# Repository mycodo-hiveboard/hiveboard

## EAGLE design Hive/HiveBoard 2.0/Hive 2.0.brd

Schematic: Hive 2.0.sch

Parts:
C1, C5: 470uF; PANASONIC_C
C1A1, C1A2, C1B1, C1B2: 1uf 50v; UD-4X5,8_NICHICON
C2, C3, C6, C9: 100uF; PANASONIC_C
C4, C18: 470pF; 0805
C7: 10uF; 0402
C8, C10, C11, C12, C13, C14, C15, C16, C17: 0.1uF; 0805
D1, D2: 1N5819-B; DO41-7.6
D4, D6, D8, D10, D12, D14, D16, D18, D20, D22, D24, D26: 1N4148; SOD-323
D5, D7, D9, D11, D13, D15, D17, D19, D21, D23, D25, D27: RED; CHIPLED_0805_NOOUTLINE
H1, H2, H3, H4: STAND-OFF
IC2: LTC4311_SC70; SC70-6L
J1, J3: C2886705; 1X04
J6, J7: Vertical Qwiic Connector; JST04_1MM_VERT
J8: POWER_JACK; POWER_JACK_PTH
JP1, JP2, JP3: HEADER-1X3ROUND; 1X03_ROUND
JP4, JP32, JP33: HEADER-1X12MM; 1X01_2MM
JP5, JP6, JP7, JP8, JP9, JP10, JP12, JP13, JP14, JP15, JP16, JP17, JP18, JP19: C2886705; 1X03-CLEANBIG
JP11, JP20, JP21, JP22, JP23, JP24, JP25, JP26, JP27, JP28, JP29, JP30: PINHD-1X3; 1X03
JP31: JUMPER3
JP34, JP35: HEADER-1X2ROUND; 1X02_ROUND
JP38, JP39: PINHD-1X19; 1X19
L1, L3: 220uH; L3216C
L2, L4: 1uH; L3216C
PS1, PS2, PS3, PS4: RFM-0505S; CONV_RFM-0505S
Q3, Q5, Q6, Q7, Q8, Q9, Q10, Q11, Q12, Q13, Q14, Q15: MMBT2222; SOT23-R
R1: 1K; M0805
R1A1, R1A2, R1B1, R1B2, R2A1, R2A2, R2B1, R2B2: 100kΩ; M1206
R2: 3K; M0805
R3, R19: 0.33R; M0805
R4, R5, R10, R11: 200KΩ; R0402
R4A1, R4A2, R4B1, R4B2: 75kΩ; M1206
R5A1, R5A2, R5B1, R5B2: 10kΩ; M1206
R6, R7: 2.4k; 0309/12
R8: 2.2K; M0805
R9: 10K; RESPACK_4X0603
R12, R14: 100KΩ; RESPACK_4X0603
R13, R16, R17, R18, R20, R21: 10KΩ; RESPACK_4X0603
R15: 1.2K; M0805
R26, R28, R29, R31, R32, R34, R35, R37, R38, R40, R41, R43, R44, R46, R47, R49, R50, R52, R53, R55, R56, R58, R59, R61: 1K; 0402
R27, R30, R33, R36, R39, R42, R45, R48, R51, R54, R57, R60: 10K; 0402
SJ2, SJ3, SJ4, SJ5, SJ6, SJ7, SJ8, SJ9, SJ10, SJ11, SJ12, SJ13: SOLDERJUMPER_CLOSED; SOLDERJUMPER_CLOSEDWIRE
U1: MCP23017-E/SO; SOIC127P1030X265-28N
U2, U3: LM358; SO08
U4, U5: MC34063ADR; D8
U$2: ESP32
X1: PWM2; JST-XH-02-PACKAGE-LONG-PAD
X2: PWM1; JST-XH-02-PACKAGE-LONG-PAD
X3, X11, X14, X17, X22: jst-xh-2; JST-XH-02-PACKAGE-LONG-PAD
X5, X23, X24, X25, X26, X27, X28, X29, X30, X31, X32, X33: RELAY_NONLATCHING-EE2NUH; RELAY_EE2_NOLATCH
X6: PWM3; JST-XH-02-PACKAGE-LONG-PAD
X7: PWM4; JST-XH-02-PACKAGE-LONG-PAD
X8, X10, X12, X15: ISO154X; SOIC8_150MIL
X9, X13, X16: RJ45-6L-B; RJ45-NO-SHIELD
X18, X19, X20, X21: BU-SMA-G

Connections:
3.3V: C7.1, C8.1, C9.+, C10.1, C12.1, C14.1, C16.1, D4.C, D6.C, D8.C, D10.C, D12.C, D14.C, D16.C, D18.C, D20.C, D22.C, D24.C, D26.C, IC2.1 (VCC), J1.1, J3.2, J6.3, J7.3, JP1.3, JP2.3, JP3.3, JP4.1, JP6.1, JP8.1, JP10.1, JP31.3, JP32.1, JP33.1, JP34.1, L4.2, R9.7 (2), R9.8 (2), R12.6 (2), R12.7 (2), R13.6 (2), R13.7 (2), R17.6 (2), R17.7 (2), R20.6 (2), R20.7 (2), R28.2, R31.2, R34.2, R37.2, R40.2, R43.2, R46.2, R49.2, R52.2, R55.2, R58.2, R61.2, U1.9 (VDD), U1.18 (!RESET), X5.1, X8.1 (VCC1), X9.4, X10.1 (VCC1), X12.1 (VCC1), X13.4, X15.1 (VCC1), X16.4, X23.1, X24.1, X25.1, X26.1, X27.1, X28.1, X29.1, X30.1, X31.1, X32.1, X33.1
+5V: C3.+, JP11.3, JP20.3, JP21.3, JP22.3, JP23.3, JP24.3, JP25.3, JP26.3, JP27.3, JP28.3, JP29.3, JP30.3, JP35.1, JP38.19, L2.2, PS1.2 (+VIN), PS2.2 (+VIN), PS3.2 (+VIN), PS4.2 (+VIN), U$2.5V
+12V: C2.+, C6.+, J8.PWR, JP11.1, JP20.1, JP21.1, JP22.1, JP23.1, JP24.1, JP25.1, JP26.1, JP27.1, JP28.1, JP29.1, JP30.1, R3.1, R19.1, U2.8 (P$V+), U3.8 (P$V+), U4.6 (VCC), U5.6 (VCC)
EN: IC2.3 (EN), R9.6 (2)
GND: C1.-, C1A1.-, C1A2.-, C1B1.-, C1B2.-, C2.-, C3.-, C4.2, C5.-, C6.-, C7.2, C8.2, C9.-, C10.2, C12.2, C14.2, C16.2, C18.2, D1.A, D2.A, IC2.2 (GND), IC2.5 (GND), J1.2, J3.1, J6.4, J7.4, J8.GND, J8.GNDBREAK, JP1.1, JP2.1, JP3.1, JP5.3, JP7.3, JP9.3, JP31.1, JP34.2, JP35.2, JP38.14, JP39.1, JP39.7, PS1.1 (-VIN), PS2.1 (-VIN), PS3.1 (-VIN), PS4.1 (-VIN), Q3.2 (E), Q5.2 (E), Q6.2 (E), Q7.2 (E), Q8.2 (E), Q9.2 (E), Q10.2 (E), Q11.2 (E), Q12.2 (E), Q13.2 (E), Q14.2 (E), Q15.2 (E), R1.1, R2A1.1, R2A2.1, R2B1.2, R2B2.2, R5A1.2, R5A2.2, R5B1.2, R5B2.2, R15.1, R27.1, R30.1, R33.1, R36.1, R39.1, R42.1, R45.1, R48.1, R51.1, R54.1, R57.1, R60.1, U1.10 (VSS), U2.4 (P$V-), U3.4 (P$V-), U4.4 (GND), U5.4 (GND), U$2.GND1, U$2.GND2, U$2.GND3, X1.2, X2.2, X6.2, X7.2, X8.4 (GND1), X9.2, X10.4 (GND1), X12.4 (GND1), X13.2, X15.4 (GND1), X16.2, X22.1
I2CVCC: X22.2
IN-PUMP-1: R26.1, U1.21 (GPA0)
IN-PUMP-2: R29.1, U1.22 (GPA1)
IN-PUMP-3: R32.1, U1.23 (GPA2)
IN-PUMP-4: R35.1, U1.24 (GPA3)
IN-PUMP-5: R38.1, U1.25 (GPA4)
IN-PUMP-6: R41.1, U1.26 (GPA5)
IN-PUMP-7: R44.1, U1.27 (GPA6)
IN-PUMP-8: R47.1, U1.28 (GPA7)
IN-PUMP-9: R50.1, U1.1 (GPB0)
IN-PUMP-10: R53.1, U1.2 (GPB1)
IN-PUMP-11: R59.1, U1.3 (GPB2)
IN-PUMP-12: R56.1, U1.4 (GPB3)
IN-PWM-1: R1A1.2, R5A1.1, U1.5 (GPB4)
IN-PWM-2: R1B1.1, R5B1.1, U1.6 (GPB5)
IN-PWM-3: R1A2.2, R5A2.1, U1.7 (GPB6)
IN-PWM-4: R1B2.1, R5B2.1, U1.8 (GPB7)
ISO-1-5V: C11.1, JP13.1, PS1.4 (+VOUT), R14.6 (2), R14.7 (2), X8.8 (VCC2)
ISO-2-5V: C13.1, JP15.1, PS2.4 (+VOUT), R16.6 (2), R16.7 (2), X10.8 (VCC2)
ISO-3-5V: C15.1, JP17.1, PS3.4 (+VOUT), R18.6 (2), R18.7 (2), X12.8 (VCC2)
ISO-4-5V: C17.1, JP19.1, PS4.4 (+VOUT), R21.6 (2), R21.7 (2), X15.8 (VCC2)
ISO-GND-1: C11.2, JP12.3, PS1.3 (-VOUT), X8.5 (GND2)
ISO-GND-2: C13.2, JP14.3, PS2.3 (-VOUT), X10.5 (GND2)
ISO-GND-3: C15.2, JP16.3, PS3.3 (-VOUT), X12.5 (GND2)
ISO-GND-4: C17.2, JP18.3, PS4.3 (-VOUT), X15.5 (GND2)
ISO-PRB-1+: JP13.2, X18.1
ISO-PRB-1GND: JP13.3, X18.2, X18.3 (2), X18.4 (2), X18.5 (2)
ISO-PRB-2+: JP15.2, X19.1
ISO-PRB-2GND: JP15.3, X19.2, X19.3 (2), X19.4 (2), X19.5 (2)
ISO-PRB-3+: JP17.2, X20.1
ISO-PRB-3GND: JP17.3, X20.2, X20.3 (2), X20.4 (2), X20.5 (2)
ISO-PRB-4+: JP19.2, X21.1
ISO-PRB-4GND: JP19.3, X21.2, X21.3 (2), X21.4 (2), X21.5 (2)
unnamed: C1A1.+, R1A1.1, R4A2.1
unnamed: D1.C, L1.1, U4.2 (SWITCHEMITTER)
unnamed: C1.+, L1.2, L2.1, R2.1
unnamed: C4.1, U4.3 (TIMINGCAPACITOR)
unnamed: C1B1.+, R1B1.2, R4B1.1
unnamed: R2A1.2, R4.1, U2.6 (-IN)
unnamed: R1.2, R2.2, U4.5 (COMPARATORINVERTINGINPUT)
unnamed: R2B1.1, R5.1, U2.2 (-IN)
unnamed: R3.2, U4.1 (SWITCHCOLLECTOR), U4.7 (IPK), U4.8 (DRIVERCOLLECTOR)
unnamed: R4A2.2, U2.5 (+IN)
unnamed: R4B1.2, U2.3 (+IN)
unnamed: D2.C, L3.1, U5.2 (SWITCHEMITTER)
unnamed: D4.A, Q3.3 (C), SJ2.1, X5.12 (2)
unnamed: Q3.1 (B), R26.2, R27.2
unnamed: D6.A, Q5.3 (C), SJ3.1, X23.12 (2)
unnamed: D5.A, R28.1
unnamed: D5.C, SJ2.2
unnamed: Q5.1 (B), R29.2, R30.2
unnamed: D8.A, Q6.3 (C), SJ4.1, X24.12 (2)
unnamed: D7.A, R31.1
unnamed: D7.C, SJ3.2
unnamed: C18.1, U5.3 (TIMINGCAPACITOR)
unnamed: Q6.1 (B), R32.2, R33.2
unnamed: R8.2, R15.2, U5.5 (COMPARATORINVERTINGINPUT)
unnamed: R19.2, U5.1 (SWITCHCOLLECTOR), U5.7 (IPK), U5.8 (DRIVERCOLLECTOR)
unnamed: C5.+, L3.2, L4.1, R8.1
unnamed: D10.A, Q7.3 (C), SJ5.1, X25.12 (2)
unnamed: D9.A, R34.1
unnamed: D9.C, SJ4.2
unnamed: Q7.1 (B), R35.2, R36.2
unnamed: D12.A, Q8.3 (C), SJ6.1, X26.12 (2)
unnamed: D11.A, R37.1
unnamed: D11.C, SJ5.2
unnamed: Q8.1 (B), R38.2, R39.2
unnamed: D14.A, Q9.3 (C), SJ7.1, X27.12 (2)
unnamed: D13.A, R40.1
unnamed: D13.C, SJ6.2
unnamed: Q9.1 (B), R41.2, R42.2
unnamed: D16.A, Q10.3 (C), SJ8.1, X28.12 (2)
unnamed: D15.A, R43.1
unnamed: D15.C, SJ7.2
unnamed: Q10.1 (B), R44.2, R45.2
unnamed: D18.A, Q11.3 (C), SJ9.1, X29.12 (2)
unnamed: D17.A, R46.1
unnamed: D17.C, SJ8.2
unnamed: Q11.1 (B), R47.2, R48.2
unnamed: D20.A, Q12.3 (C), SJ10.1, X30.12 (2)
unnamed: D19.A, R49.1
unnamed: D19.C, SJ9.2
unnamed: Q12.1 (B), R50.2, R51.2
unnamed: D22.A, Q13.3 (C), SJ11.1, X31.12 (2)
unnamed: D21.A, R52.1
unnamed: C1A2.+, R1A2.1, R4A1.1
unnamed: C1B2.+, R1B2.2, R4B2.1
unnamed: R2A2.2, R10.1, U3.6 (-IN)
unnamed: R2B2.1, R11.1, U3.2 (-IN)
unnamed: R4A1.2, U3.5 (+IN)
unnamed: R4B2.2, U3.3 (+IN)
unnamed: D21.C, SJ10.2
unnamed: Q13.1 (B), R53.2, R54.2
unnamed: D24.A, Q14.3 (C), SJ12.1, X32.12 (2)
unnamed: D23.A, R55.1
unnamed: D23.C, SJ11.2
unnamed: Q14.1 (B), R56.2, R57.2
unnamed: JP38.1, U$2.3.3V
unnamed: D25.A, R58.1
unnamed: D25.C, SJ12.2
unnamed: JP38.2, U$2.EN
unnamed: D26.A, Q15.3 (C), SJ13.1, X33.12 (2)
unnamed: Q15.1 (B), R59.2, R60.2
unnamed: JP38.3, U$2.GPIO36
unnamed: D27.A, R61.1
unnamed: D27.C, SJ13.2
unnamed: JP1.2, U1.15 (A0)
unnamed: JP2.2, U1.16 (A1)
unnamed: JP3.2, U1.17 (A2)
unnamed: JP38.4, U$2.GPIO39
unnamed: JP38.5, U$2.GPIO34
unnamed: JP38.6, U$2.GPIO35
unnamed: JP38.7, U$2.GPIO32
unnamed: JP38.8, U$2.GPIO33
unnamed: JP38.9, U$2.GPIO25
unnamed: JP38.10, U$2.GPIO26
unnamed: JP38.11, U$2.GPIO27
unnamed: JP38.12, U$2.GPIO14
unnamed: JP38.13, U$2.GPIO12
unnamed: JP31.2, R9.3 (1)
unnamed: JP38.16, U$2.GPIO9
unnamed: JP38.15, U$2.GPIO13
unnamed: JP38.17, U$2.GPIO10
unnamed: JP38.18, U$2.GPIO11
unnamed: JP39.19, U$2.GPIO6
unnamed: JP39.18, U$2.GPIO7
unnamed: JP39.17, U$2.GPIO8
unnamed: JP39.16, U$2.GPIO15
unnamed: JP39.15, U$2.GPIO2
unnamed: JP39.14, U$2.GPIO0
unnamed: JP39.13, U$2.GPIO4
unnamed: JP39.12, U$2.GPIO16
unnamed: JP39.11, U$2.GPIO17
unnamed: JP39.10, U$2.GPIO5
unnamed: JP39.9, U$2.GPIO18
unnamed: JP39.8, U$2.GPIO19
unnamed: JP39.5, U$2.RX
unnamed: JP39.4, U$2.TX
unnamed: JP39.2, U$2.GPIO23
NISO-PRB-1+: JP6.2, X11.2
NISO-PRB-1GND: JP6.3, X11.1
NISO-PRB-2+: JP8.2, X14.2
NISO-PRB-2GND: JP8.3, X14.1
NISO-PRB-3+: JP10.2, X17.2
NISO-PRB-3GND: JP10.3, X17.1
PWM-OUT-1: R4.2, U2.7 (OUT), X2.1
PWM-OUT-2: R5.2, U2.1 (OUT), X1.1
PWM-OUT-3: R10.2, U3.7 (OUT), X6.1
PWM-OUT-4: R11.2, U3.1 (OUT), X7.1
RELAY1PWRIN: JP11.2, X5.9 (P1)
RELAY1PWROUT: X5.8 (S1), X9.1
RELAY2PWRIN: JP20.2, X23.9 (P1)
RELAY2PWROUT: X9.3, X23.8 (S1)
RELAY3PWRIN: JP21.2, X24.9 (P1)
RELAY3PWROUT: X9.5, X24.8 (S1)
RELAY4PWRIN: JP22.2, X25.9 (P1)
RELAY4PWROUT: X9.7, X25.8 (S1)
RELAY5PWRIN: JP23.2, X26.9 (P1)
RELAY5PWROUT: X13.1, X26.8 (S1)
RELAY6PWRIN: JP25.2, X28.9 (P1)
RELAY6PWROUT: X13.3, X27.8 (S1)
RELAY7PWRIN: JP24.2, X27.9 (P1)
RELAY7PWROUT: X13.5, X28.8 (S1)
RELAY8PWRIN: JP26.2, X29.9 (P1)
RELAY8PWROUT: X13.7, X29.8 (S1)
RELAY9PWRIN: JP27.2, X30.9 (P1)
RELAY9PWROUT: X16.1, X30.8 (S1)
RELAY10PWRIN: JP28.2, X31.9 (P1)
RELAY10PWROUT: X16.3, X31.8 (S1)
RELAY11PWRIN: JP29.2, X33.9 (P1)
RELAY11PWROUT: X16.5, X33.8 (S1)
RELAY12PWRIN: JP30.2, X32.9 (P1)
RELAY12PWROUT: X16.7, X32.8 (S1)
SCL: IC2.6 (BUS1), J1.3, J3.3, J6.1, J7.1, JP5.1, JP7.1, JP9.1, R7.2, R9.2 (1), R12.3 (1), R13.3 (1), R17.3 (1), R20.3 (1), U1.12 (SCK), X3.1, X8.3 (SCL1), X9.8, X10.3 (SCL1), X12.3 (SCL1), X13.8, X15.3 (SCL1), X16.8
SCL1: JP39.3, R7.1, U$2.GPIO22
SCL2: JP12.1, R14.3 (1), X8.6 (SCL2)
SCL3: JP14.1, R16.3 (1), X10.6 (SCL2)
SCL4: JP16.1, R18.3 (1), X12.6 (SCL2)
SCL5: JP18.1, R21.3 (1), X15.6 (SCL2)
SDA: IC2.4 (BUS2), J1.4, J3.4, J6.2, J7.2, JP5.2, JP7.2, JP9.2, R6.2, R9.1, R12.2 (1), R13.2 (1), R17.2 (1), R20.2 (1), U1.13 (SDA), X3.2, X8.2 (SDA1), X9.6, X10.2 (SDA1), X12.2 (SDA1), X13.6, X15.2 (SDA1), X16.6
SDA1: JP39.6, R6.1, U$2.GPIO21
SDA2: JP12.2, R14.2 (1), X8.7 (SDA2)
SDA3: JP14.2, R16.2 (1), X10.7 (SDA2)
SDA4: JP16.2, R18.2 (1), X12.7 (SDA2)
SDA5: JP18.2, R21.2 (1), X15.7 (SDA2)

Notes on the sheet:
Power Isolation
Pump Control
PWM to Analog
EZO connectors non-isolated
Sensor and Screen Connector
Power and Data
25 V
5 V / 500 mA
Optional Filter
VOUT = 1.25 (1 + R2/R1)
MC33063ADR_Voltage Step-Down Converter
VIN
Adjust the value of R1 and R2 to get desired output voltage
Output ripple = 500 mVPP Output ripple with optional filter = 70 mVPP
C4 is Tantalum capacitor
I2C Pullups & Shift
Power supply

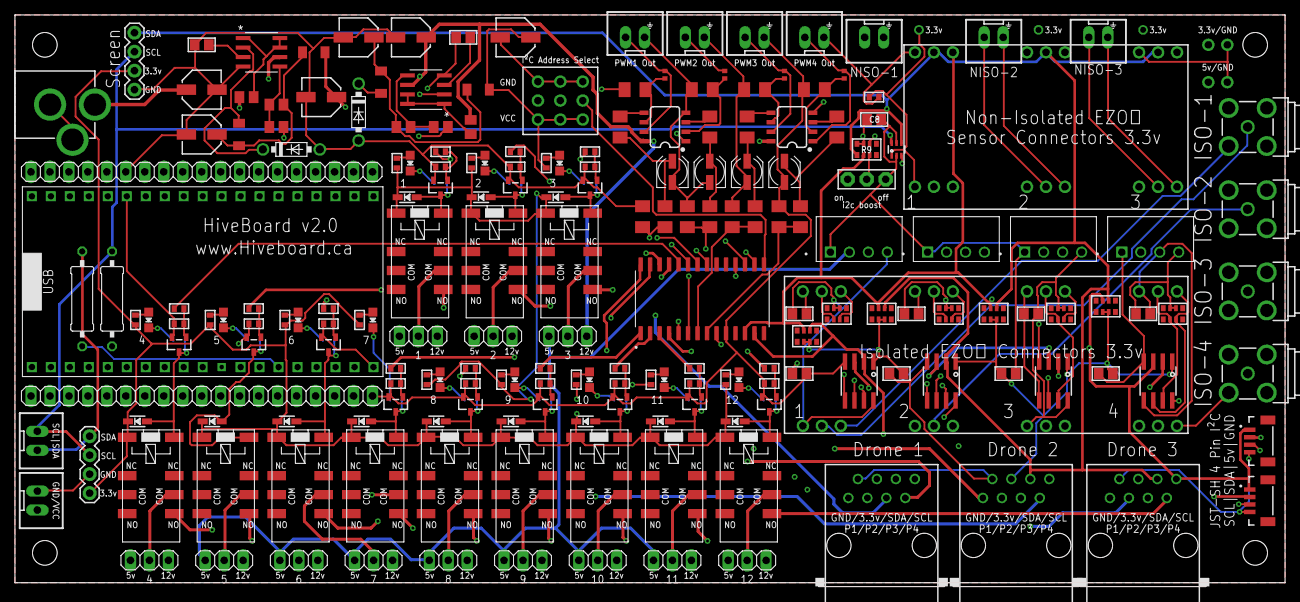
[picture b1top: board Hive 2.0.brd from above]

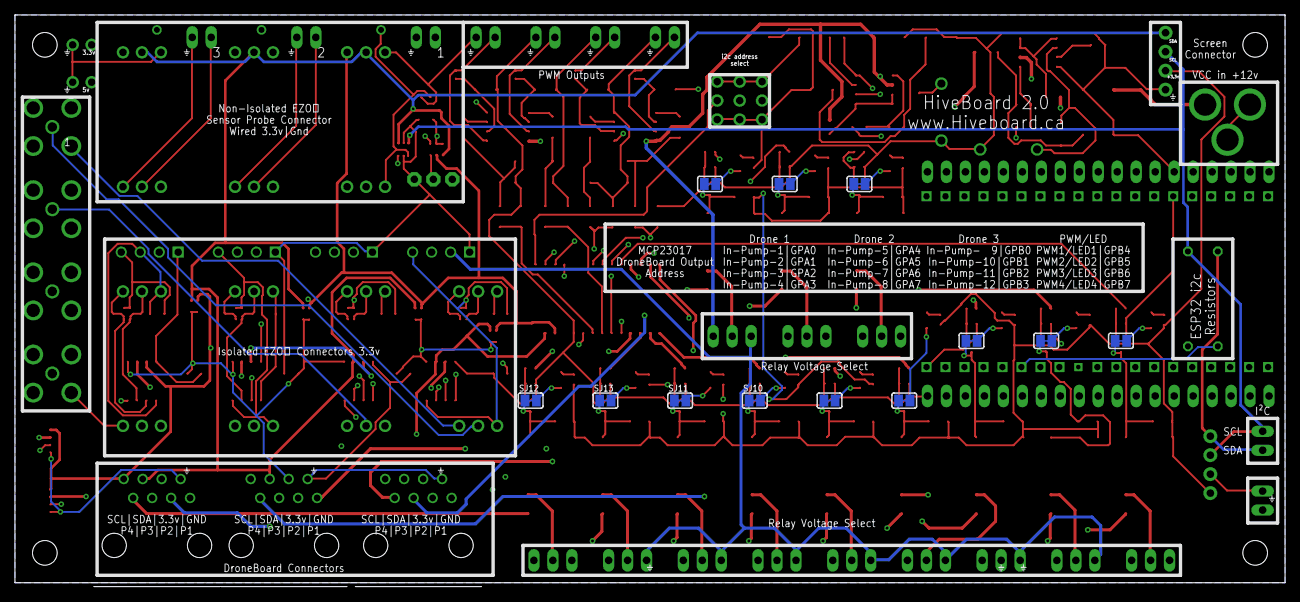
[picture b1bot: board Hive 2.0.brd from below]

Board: 4 copper layers, 170.0 x 76.5 mm, 238 parts (12 on the bottom side), 189 nets.

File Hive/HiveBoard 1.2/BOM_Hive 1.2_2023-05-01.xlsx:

No. | Quantity | Comment | Designator | Footprint | Value | Manufacturer Part | Manufacturer | Supplier Part | Supplier
1 | 2 | 470uF | C1,C5 | PANASONIC_C
2 | 4 | 1uf 50v | C1A1,C1A2,C1B1,C1B2 | UD-4X5,8_NICHICON | C3348
3 | 4 | 100uF | C2,C3,C6,C9 | PANASONIC_C | C2977467
4 | 2 | 470pF | C4,C18 | PANASONIC_C
5 | 1 | 10uF | C7 | 0805-NO
6 | 9 | 0.1uF | C8,C10,C11,C12,C13,C14,C15,C16,C17 | 0603-NO@1
7 | 2 | 1N5819-B | D1,D2 | DO41-7.6
8 | 12 | 1N4148 | D4,D6,D8,D10,D12,D14,D16,D18,D20,D22,D24,D26 | SOD-323
9 | 12 | RED | D5,D7,D9,D11,D13,D15,D17,D19,D21,D23,D25,D27 | CHIPLED_0805_NOOUTLINE
10 | 4 | STAND-OFF | H1,H2,H3,H4 | STAND-OFF
11 | 1 | LTC4311_SC70 | IC2 | SC70-6L
12 | 1 | C2886705 | J3 | 1X04 | C2886705
 | 1 |  | J1 | 1X04 | C2938451
13 | 2 | Vertical Qwiic Connector | J6,J7 | JST04_1MM_VERT | C2859067
14 | 1 | POWER_JACK | J8 | POWER_JACK_PTH | C16214
15 | 3 |  | JP1,JP2,JP3 | 1X03_ROUND | C49257
16 | 3 |  | JP4,JP32,JP33 | 1X01_2MM | C81276
17 | 14 | C2886705 | JP5,JP6,JP7,JP8,JP9,JP10,JP12,JP13,JP14,JP15,JP16,JP17,JP18,JP19 | 1X03-CLEANBIG | C2886705
18 | 12 |  | JP11,JP20,JP21,JP22,JP23,JP24,JP25,JP26,JP27,JP28,JP29,JP30 | 1X03 | C49257
19 | 1 |  | JP31 | JUMPER3 | C49257
20 | 2 |  | JP34,JP35 | 1X02_ROUND | C2905434
21 | 2 |  | JP38,JP39 | 1X19 | C725951
22 | 2 | 220uH | L1,L3 | L3216C | C222626 |  | C2929444
23 | 2 | 1uH | L2,L4 | L3216C | C5199446
24 | 4 | RFM-0505S | PS1,PS2,PS3,PS4 | CONV_RFM-0505S | C5364402
25 | 12 | MMBT2222 | Q3,Q5,Q6,Q7,Q8,Q9,Q10,Q11,Q12,Q13,Q14,Q15 | SOT23-R
26 | 2 | 1.2K | R1,R15 | M0805
27 | 8 | 100kΩ | R1A1,R1A2,R1B1,R1B2,R2A1,R2A2,R2B1,R2B2 | M1206
28 | 1 | 3.8K | R2 | M0805
29 | 2 | 0.33R | R3,R19 | M0805
30 | 4 | 200KΩ | R4,R5,R10,R11 | R0402
31 | 4 | 75kΩ | R4A1,R4A2,R4B1,R4B2 | M1206
32 | 4 | 10kΩ | R5A1,R5A2,R5B1,R5B2 | M1206
33 | 2 | 2.4k | R6,R7 | WSC0001 | C119077
34 | 1 | 2.2K | R8 | M0805
35 | 1 | 10K | R9 | RESPACK_4X0603 | C29718
36 | 2 | 100KΩ | R12,R14 | RESPACK_4X0603
37 | 6 | 10KΩ | R13,R16,R17,R18,R20,R21 | RESPACK_4X0603 | C29718
38 | 24 | 1K | R26,R28,R29,R31,R32,R34,R35,R37,R38,R40,R41,R43,R44,R46,R47,R49,R50,R52,R53,R55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 | 0805-NO
39 | 12 | 10K | R27,R30,R33,R36,R39,R42,R45,R48,R51,R54,R57,R60 | 0805-NO
40 | 12 |  | SJ2,SJ3,SJ4,SJ5,SJ6,SJ7,SJ8,SJ9,SJ10,SJ11,SJ12,SJ13 | SOLDERJUMPER_CLOSEDWIRE
41 | 1 | MCP23017-E/SO | U1 | SOIC127P1030X265-28N | C47023
42 | 2 | LM358 | U2,U3 | SO08
43 | 2 | MC34063ADR | U4,U5 | D8 | C32078
44 | 1 | ESP32 | U$2 | ESP32
45 | 1 | PWM2 | X1 | JST-XH-02-PACKAGE-LONG-PAD | C157931
46 | 1 | PWM1 | X2 | JST-XH-02-PACKAGE-LONG-PAD | C157931
47 | 5 | jst-xh-2 | X3,X11,X14,X17,X22 | JST-XH-02-PACKAGE-LONG-PAD | C157931
48 | 12 | RELAY_NONLATCHING-EE2NUH | X5,X23,X24,X25,X26,X27,X28,X29,X30,X31,X32,X33 | RELAY_EE2_NOLATCH | C147869
49 | 1 | PWM3 | X6 | JST-XH-02-PACKAGE-LONG-PAD | C157931
50 | 1 | PWM4 | X7 | JST-XH-02-PACKAGE-LONG-PAD | C157931
51 | 4 | ISO154X | X8,X10,X12,X15 | SOIC8_150MIL
52 | 3 | RJ45-6L-B | X9,X13,X16 | RJ45-NO-SHIELD | C708595
53 | 4 | BU-SMA-G | X18,X19,X20,X21 | BU-SMA-G | C411575

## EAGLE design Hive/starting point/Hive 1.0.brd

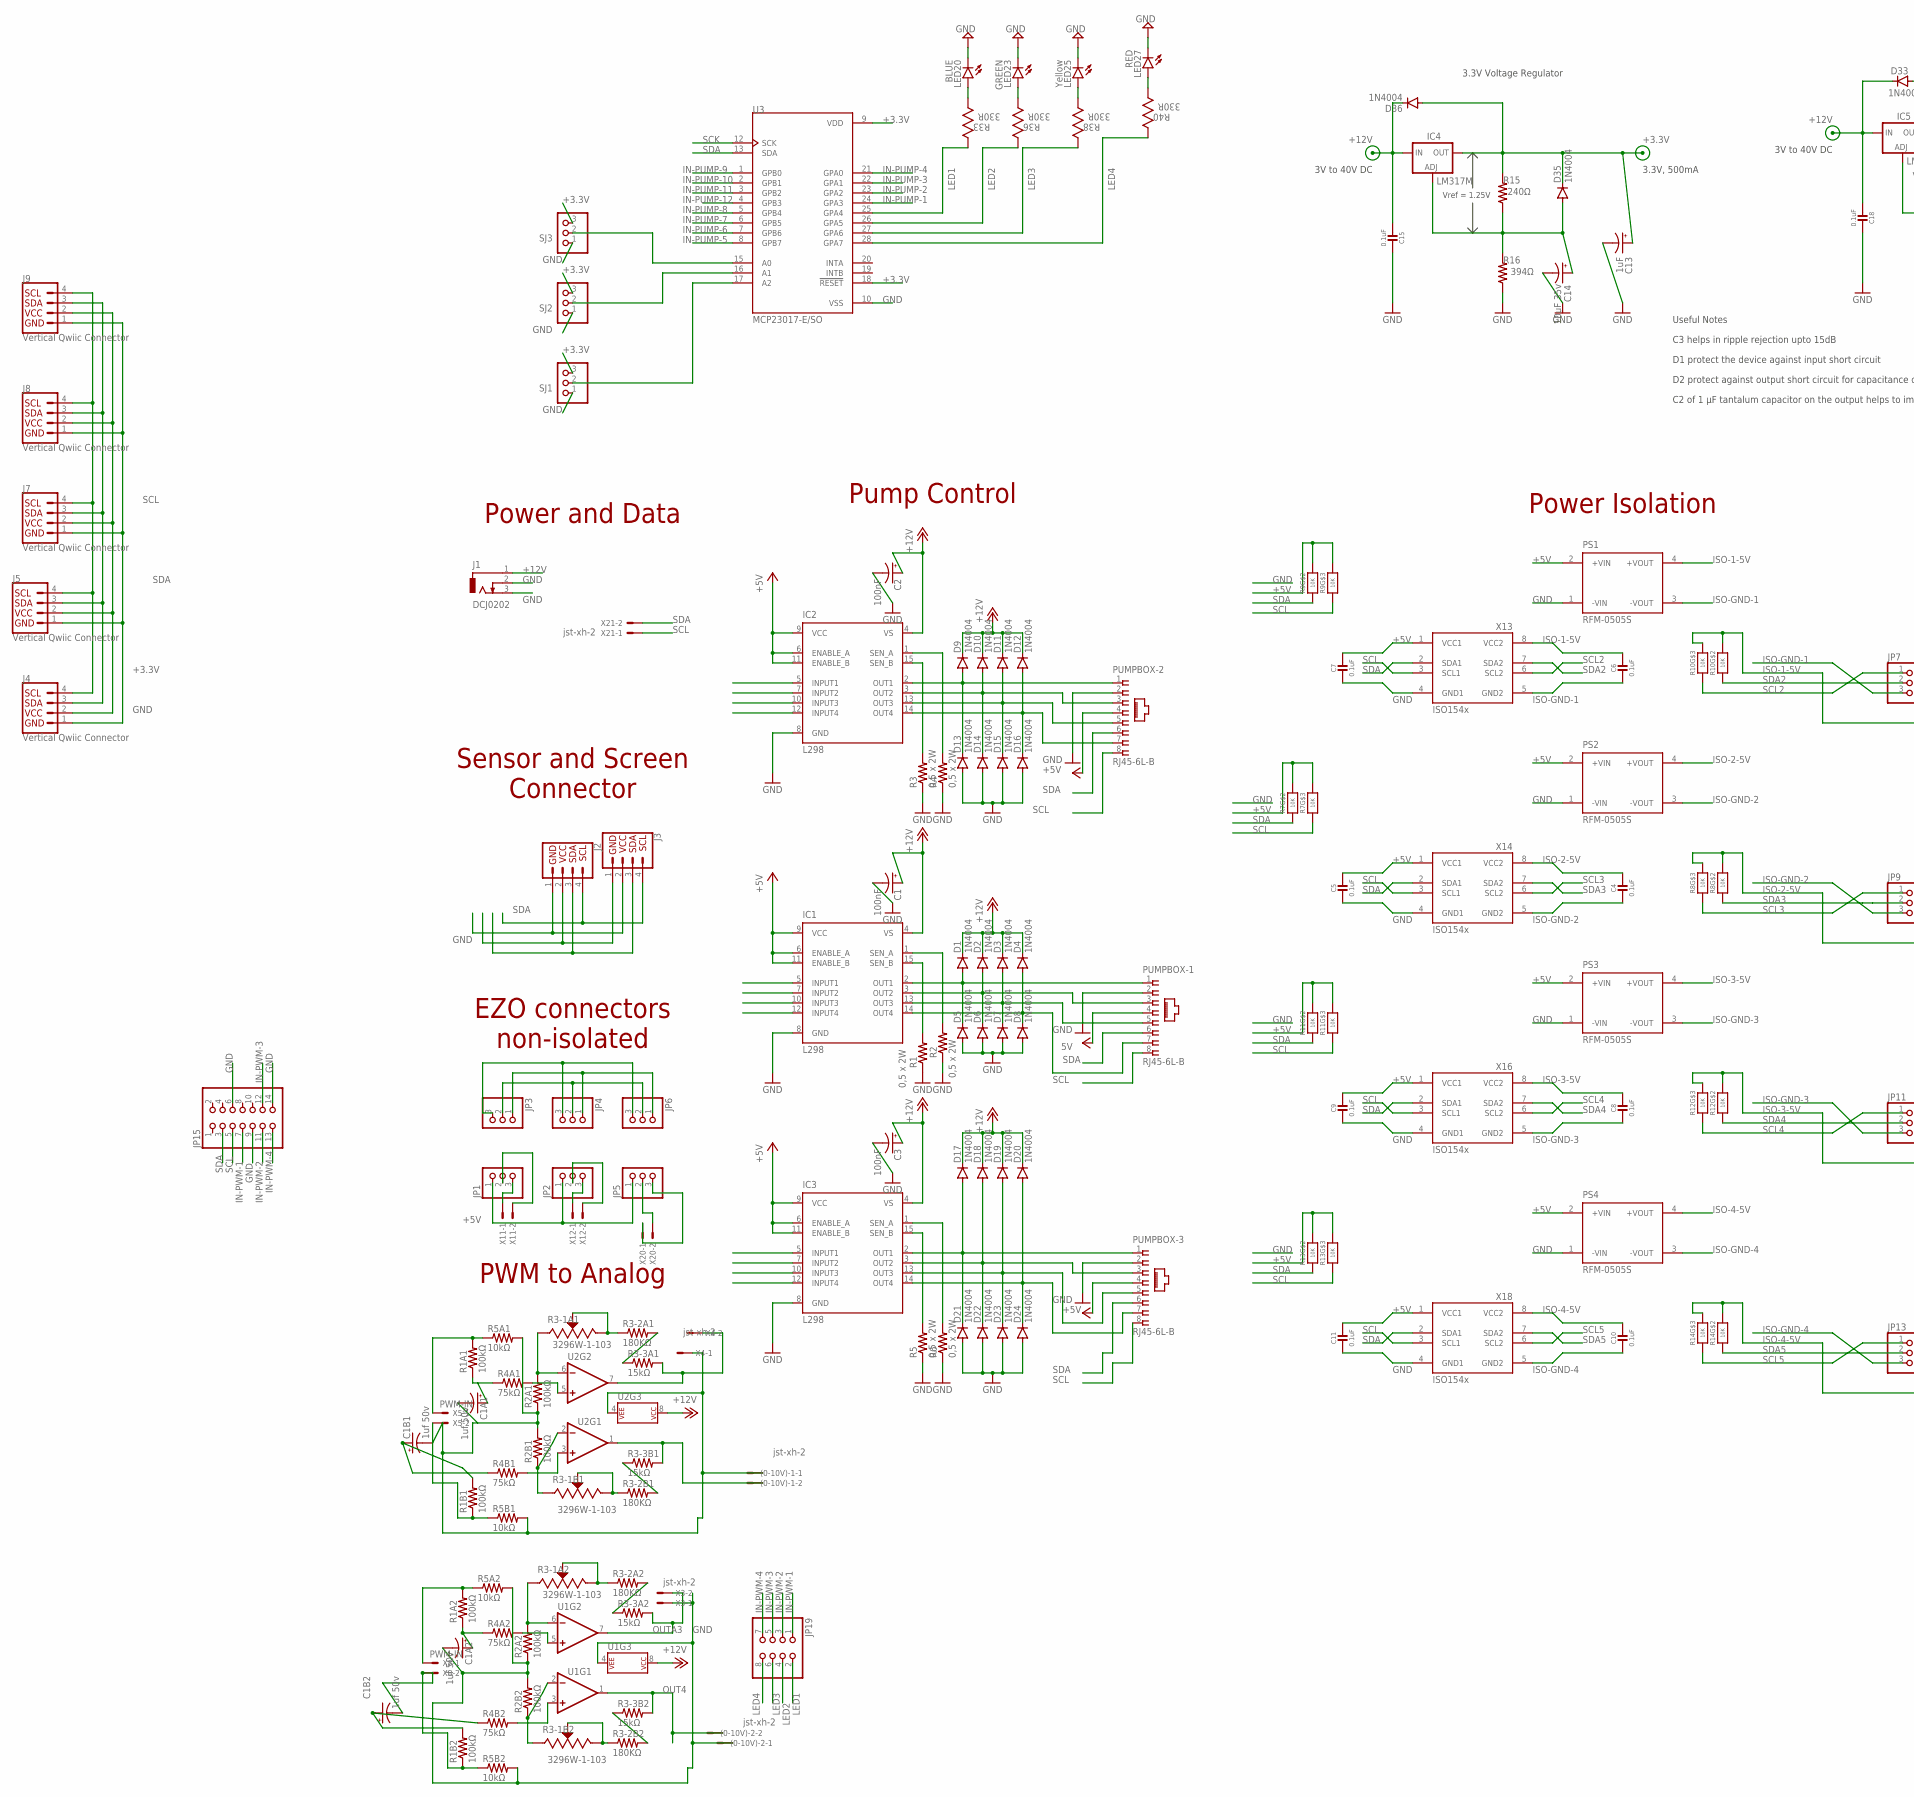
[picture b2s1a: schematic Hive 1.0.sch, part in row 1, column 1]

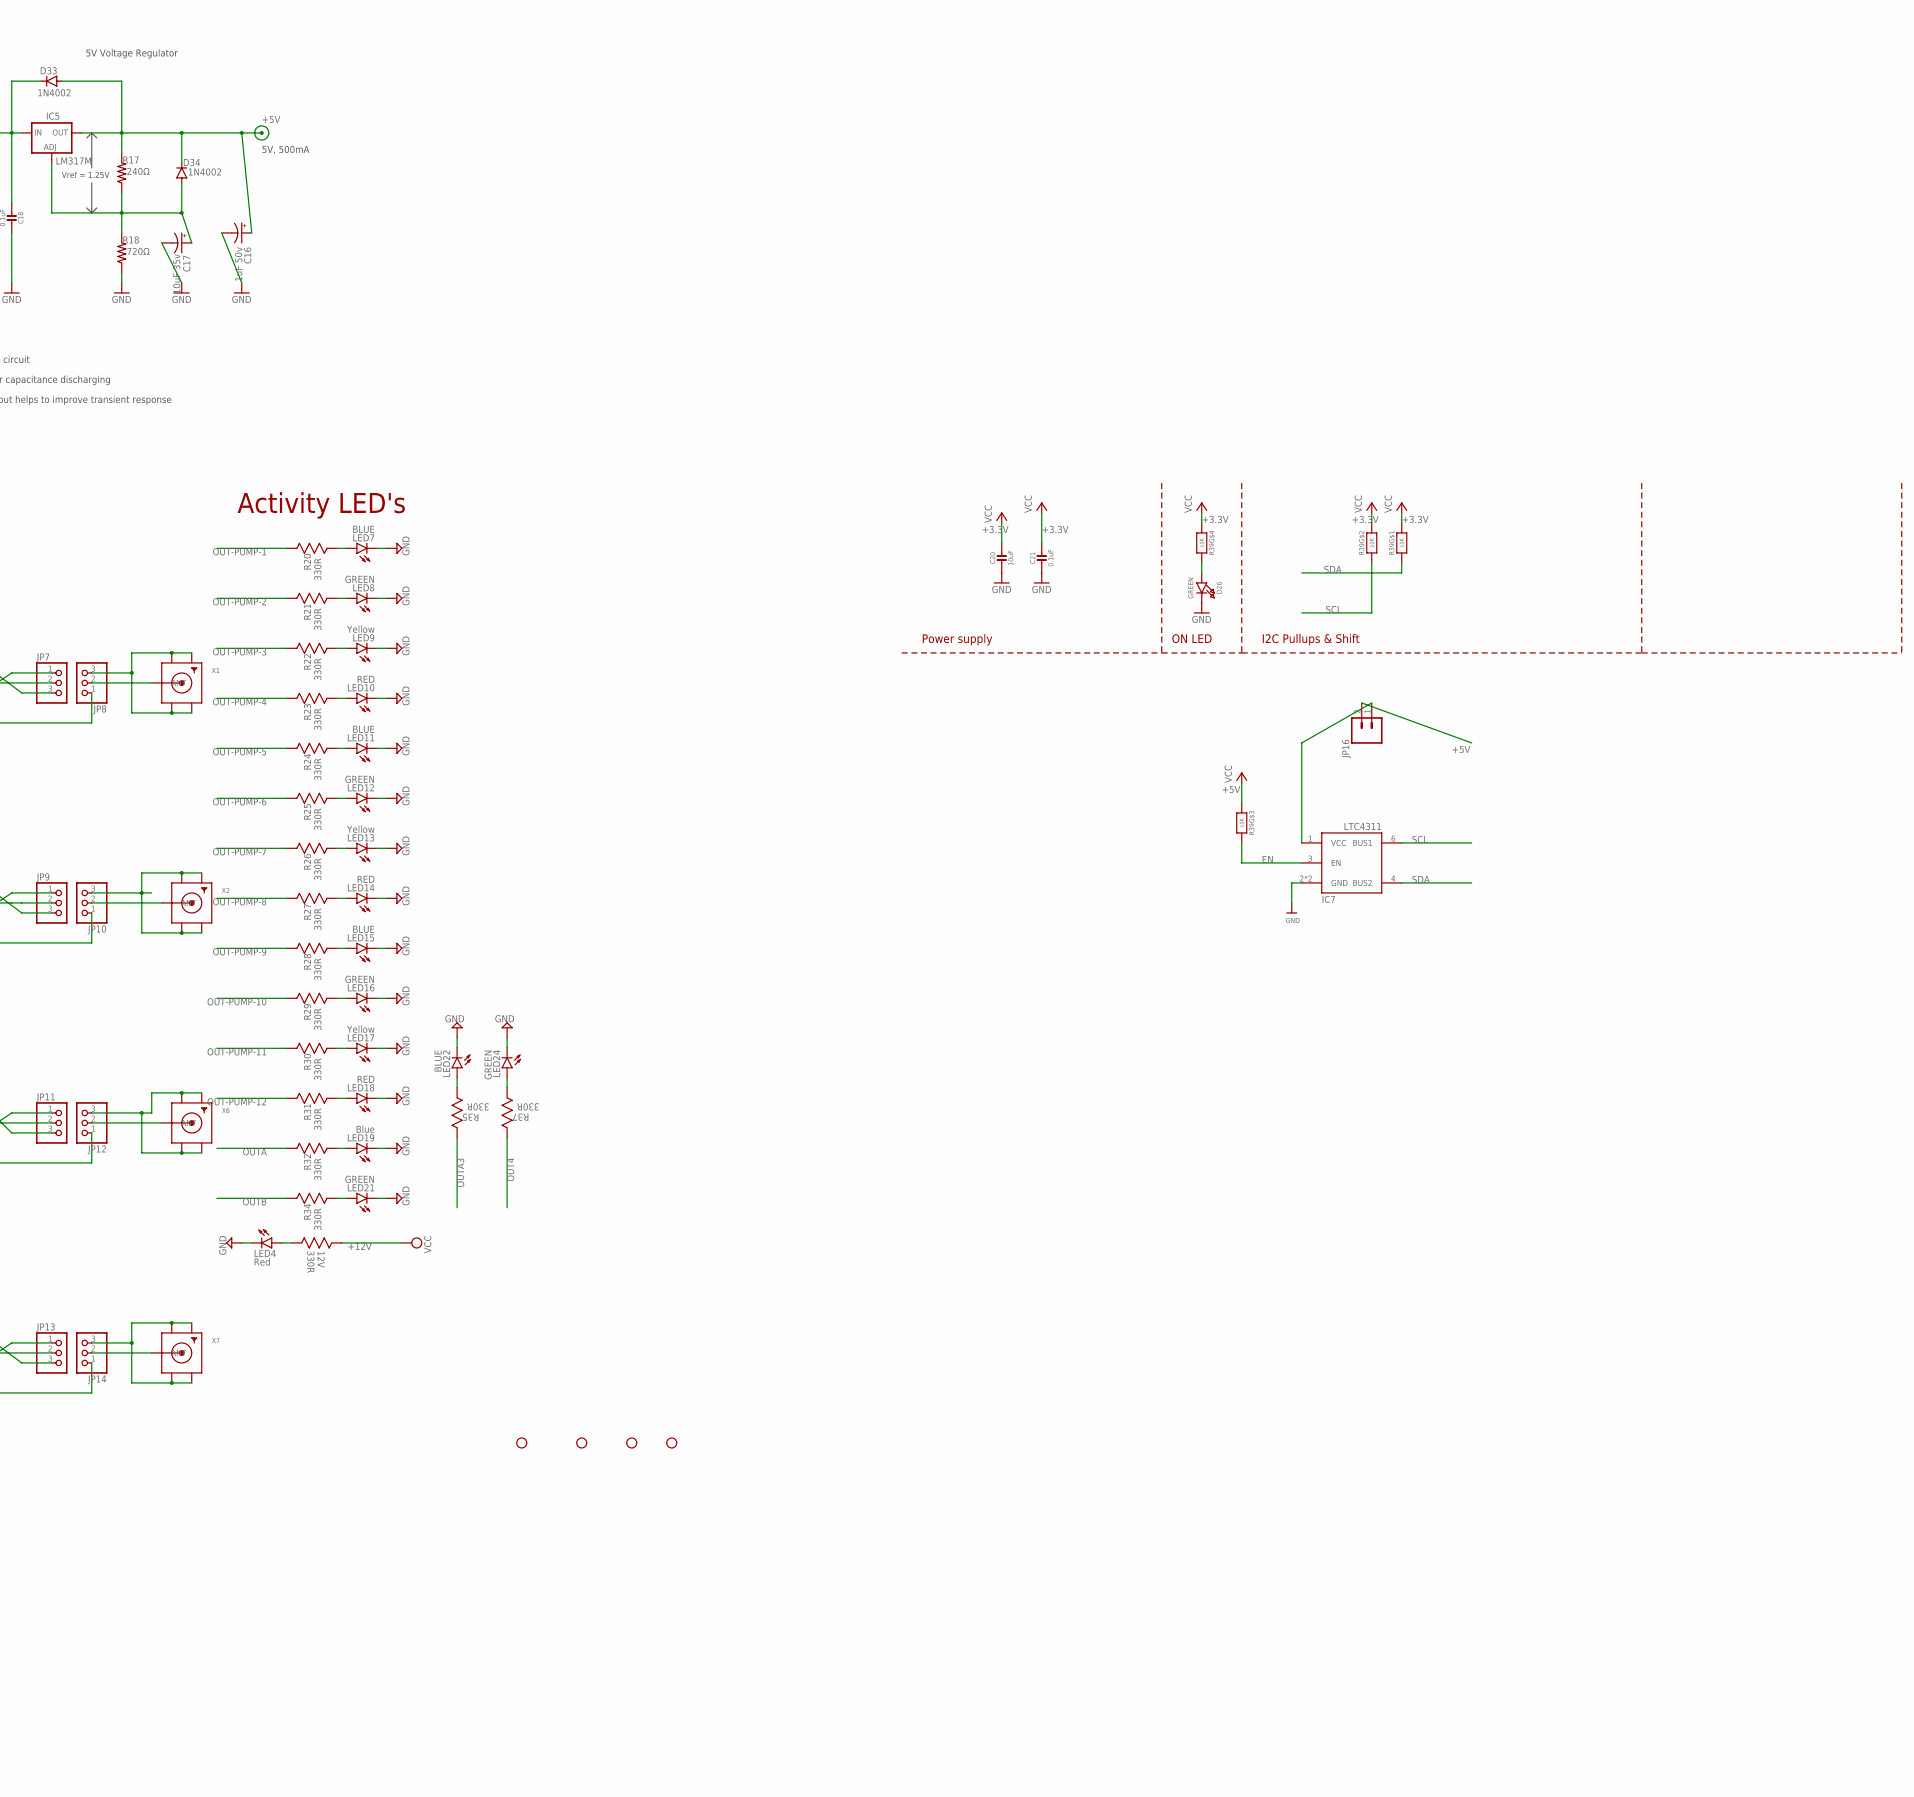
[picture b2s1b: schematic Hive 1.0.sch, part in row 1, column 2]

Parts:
12V: 330R; RESC1608X60N
(0-10V)-1, (0-10V)-2: jst-xh-2; JST-XH-02-PACKAGE-LONG-PAD
C1, C2, C3: 100nF; UD-4X5,8_NICHICON
C1A1, C1A2, C1B1, C1B2: 1uf 50v; UD-4X5,8_NICHICON
C4, C5, C6, C7, C8, C9, C10, C11, C15, C18, C21: 0.1uF; 0603-NO
C13: 1uF; UD-4X5,8_NICHICON
C14, C17: 10uF 35v; UD-4X5,8_NICHICON
C16: 1uF 50v; UD-4X5,8_NICHICON
C20: 10uF; 0805-NO
D1, D2, D3, D4, D5, D6, D7, D8, D9, D10, D11, D12, D13, D14, D15, D16, D17, D18, D19, D20, D21, D22, D23, D24, D35, D36: 1N4004; DO214BA
D26: GREEN; CHIPLED_0603_NOOUTLINE
D33, D34: 1N4002; DO214BA
H5, H6, H7, H8: STAND-OFF
IC1, IC2, IC3: L298; MULTIWATT-15
IC4, IC5: LM317MBSTT3; SOT223; PARTNUMBER LM317M
IC7: LTC4311_SC70; SC70-6L
J1: DCJ0202
J2, J3: I2C_STANDARD; 1X04
J4, J5, J7, J8, J9: Vertical Qwiic Connector; JST04_1MM_VERT
JP1, JP2, JP3, JP4, JP5, JP6, JP7, JP8, JP9, JP10, JP11, JP12, JP13, JP14: PINHD-1X3CB; 1X03-CLEANBIG
JP15: PINHD-2X7; 2X07
JP16: CONN_02; 1X02
JP19: PINHD-2X4; 2X04
LED4: Red; LED-0603
LED7, LED11, LED15, LED20, LED22: BLUE; LED-0603
LED8, LED12, LED16, LED21, LED23, LED24: GREEN; LED-0603
LED9, LED13, LED17, LED25: Yellow; LED-0603
LED10, LED14, LED18, LED27: RED; LED-0603
LED19: Blue; LED-0603
PS1, PS2, PS3, PS4: RFM-0505S; CONV_RFM-0505S
PUMPBOX-1, PUMPBOX-2, PUMPBOX-3: RJ45-6L-B; RJ45-NO-SHIELD
R1, R2, R3, R4, R5, R6: 0,5 x 2W; R2512
R1A1, R1A2, R1B1, R1B2, R2A1, R2A2, R2B1, R2B2: 100kΩ; M1206
R3-1A1, R3-1A2, R3-1B1, R3-1B2: 3296W-1-103; TRIM_3296W-1-103
R3-2A1, R3-2A2, R3-2B1, R3-2B2: 180KΩ; M1206
R3-3A1, R3-3A2, R3-3B1, R3-3B2: 15kΩ; M1206
R4A1, R4A2, R4B1, R4B2: 75kΩ; M1206
R5A1, R5A2, R5B1, R5B2: 10kΩ; M1206
R7, R8, R9, R10, R11, R12, R13, R14, R39: 10K; RESPACK_4X0603
R15, R17: 240Ω; M0805
R16: 394Ω; M0805
R18: 720Ω; M0805
R20, R21, R22, R23, R24, R25, R26, R27, R28, R29, R30, R31, R32, R33, R34, R35, R36, R37, R38, R40: 330R; RESC1608X60N
SJ1, SJ2, SJ3: PINHD-1X3; 1X03
U1, U2: LM358; SO08
U3: MCP23017-E/SO; SOIC127P1030X265-28N
X1, X2, X6, X7: SMACONNECTOR_EDGE; SMA_EDGELAUNCH
X3, X4, X11, X12, X20, X21: jst-xh-2; JST-XH-02-PACKAGE-LONG-PAD
X5, X8: PWM-IN; JST-XH-02-PACKAGE-LONG-PAD
X13, X14, X16, X18: ISO154X; SOIC8_150MIL

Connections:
+3.3V: C13.+, C20.1, C21.1, D35.C, D36.A, IC4.4 (OUT), J4.2, J5.2, J7.2, J8.2, J9.2, R15.2, R39.4 (1), R39.7 (2), R39.8 (2), SJ1.3, SJ2.3, SJ3.3, U3.9 (VDD), U3.18 (!RESET)
+5V: C5.1, C7.1, C9.1, C11.1, C16.+, D33.A, D34.C, IC1.6 (ENABLE_A), IC1.9 (VCC), IC1.11 (ENABLE_B), IC2.6 (ENABLE_A), IC2.9 (VCC), IC2.11 (ENABLE_B), IC3.6 (ENABLE_A), IC3.9 (VCC), IC3.11 (ENABLE_B), IC5.4 (OUT), J2.1, J3.2, JP1.1, JP2.1, JP5.1, JP16.2, PS1.2 (+VIN), PS2.2 (+VIN), PS3.2 (+VIN), PS4.2 (+VIN), PUMPBOX-1.4, PUMPBOX-2.4, PUMPBOX-3.4, R7.6 (2), R7.7 (2), R9.6 (2), R9.7 (2), R11.6 (2), R11.7 (2), R13.6 (2), R13.7 (2), R17.2, R39.3 (1), X13.1 (VCC1), X14.1 (VCC1), X16.1 (VCC1), X18.1 (VCC1)
+12V: 12V.1 (R1), C1.+, C2.+, C3.+, C15.2, C18.2, D1.C, D2.C, D3.C, D4.C, D9.C, D10.C, D11.C, D12.C, D17.C, D18.C, D19.C, D20.C, D33.C, D36.C, IC1.4 (VS), IC2.4 (VS), IC3.4 (VS), IC4.3 (IN), IC5.3 (IN), J1.1, U1.8 (P$V+), U2.8 (P$V+)
EN: IC7.3 (EN), R39.6 (2)
GND: (0-10V)-1.1, (0-10V)-2.1, C1.-, C1A1.-, C1A2.-, C1B1.-, C2.-, C3.-, C5.2, C7.2, C9.2, C11.2, C13.-, C14.-, C15.1, C16.-, C17.-, C18.1, C20.2, C21.2, D5.A, D6.A, D7.A, D8.A, D13.A, D14.A, D15.A, D16.A, D21.A, D22.A, D23.A, D24.A, D26.C, IC1.8 (GND), IC2.8 (GND), IC3.8 (GND), IC7.2 (GND), IC7.5 (GND), J1.2, J1.3, J2.2, J3.1, J4.1, J5.1, J7.1, J8.1, J9.1, JP3.3, JP4.3, JP6.3, JP15.6, JP15.9, JP15.14, LED4.C, LED7.C, LED8.C, LED9.C, LED10.C, LED11.C, LED12.C, LED13.C, LED14.C, LED15.C, LED16.C, LED17.C, LED18.C, LED19.C, LED20.C, LED21.C, LED22.C, LED23.C, LED24.C, LED25.C, LED27.C, PS1.1 (-VIN), PS2.1 (-VIN), PS3.1 (-VIN), PS4.1 (-VIN), PUMPBOX-1.2, PUMPBOX-2.2, PUMPBOX-3.2, R1.1, R2.1, R2A1.1, R2A2.1, R2B1.2, R2B2.2, R3.1, R4.1, R5.1, R5A1.2, R5A2.2, R5B1.2, R5B2.2, R6.1, R16.1, R18.1, SJ1.1, SJ2.1, SJ3.1, U1.4 (P$V-), U2.4 (P$V-), U3.10 (VSS), X3.1, X4.1, X13.4 (GND1), X14.4 (GND1), X16.4 (GND1), X18.4 (GND1)
IN-PUMP-1: IC1.5 (INPUT1), U3.24 (GPA3)
IN-PUMP-2: IC1.7 (INPUT2), U3.23 (GPA2)
IN-PUMP-3: IC1.10 (INPUT3), U3.22 (GPA1)
IN-PUMP-4: IC1.12 (INPUT4), U3.21 (GPA0)
IN-PUMP-5: IC2.5 (INPUT1), U3.8 (GPB7)
IN-PUMP-6: IC2.7 (INPUT2), U3.7 (GPB6)
IN-PUMP-7: IC2.10 (INPUT3), U3.6 (GPB5)
IN-PUMP-8: IC2.12 (INPUT4), U3.5 (GPB4)
IN-PUMP-9: IC3.5 (INPUT1), U3.1 (GPB0)
IN-PUMP-10: IC3.7 (INPUT2), U3.2 (GPB1)
IN-PUMP-11: IC3.10 (INPUT3), U3.3 (GPB2)
IN-PUMP-12: IC3.12 (INPUT4), U3.4 (GPB3)
IN-PWM-1: JP15.7, JP19.1, R1A1.2, R5A1.1, X5.1
IN-PWM-2: JP15.11, JP19.3, R1B1.1, R5B1.1, X5.2
IN-PWM-3: JP15.12, JP19.5, R1A2.2, R5A2.1, X8.1
IN-PWM-4: C1B2.-, JP15.13, JP19.7, R1B2.1, R5B2.1, X8.2
ISO-1-5V: C6.1, JP8.1, PS1.4 (+VOUT), R10.6 (2), R10.7 (2), X13.8 (VCC2)
ISO-2-5V: C4.1, JP10.1, PS2.4 (+VOUT), R8.6 (2), R8.7 (2), X14.8 (VCC2)
ISO-3-5V: C8.1, JP12.1, PS3.4 (+VOUT), R12.6 (2), R12.7 (2), X16.8 (VCC2)
ISO-4-5V: C10.1, JP14.1, PS4.4 (+VOUT), R14.6 (2), R14.7 (2), X18.8 (VCC2)
ISO-GND-1: C6.2, JP7.3, PS1.3 (-VOUT), X13.5 (GND2)
ISO-GND-2: C4.2, JP9.3, PS2.3 (-VOUT), X14.5 (GND2)
ISO-GND-3: C8.2, JP11.3, PS3.3 (-VOUT), X16.5 (GND2)
ISO-GND-4: C10.2, JP13.3, PS4.3 (-VOUT), X18.5 (GND2)
LED1: JP19.2, R33.1 (R1), U3.25 (GPA4)
LED2: JP19.4, R36.1 (R1), U3.26 (GPA5)
LED3: JP19.6, R38.1 (R1), U3.27 (GPA6)
LED4: JP19.8, R40.1 (R1), U3.28 (GPA7)
unnamed: IC2.1 (SEN_A), R4.2
unnamed: IC2.15 (SEN_B), R3.2
unnamed: IC3.1 (SEN_A), R6.2
unnamed: IC3.15 (SEN_B), R5.2
unnamed: C14.+, D35.A, IC4.1 (ADJ), R15.1, R16.2
unnamed: R3-1B2.2 (WIPER), R3-1B2.3 (CW), R3-2B2.1
unnamed: LED20.A, R33.2 (R2)
unnamed: R3-2B2.2, R3-3B2.1
unnamed: IC1.1 (SEN_A), R2.2
unnamed: IC1.15 (SEN_B), R1.2
unnamed: C17.+, D34.A, IC5.1 (ADJ), R17.1, R18.2
unnamed: JP12.3, X6.GND@1 (GND4), X6.GND@2 (GND3), X6.GND@3 (GND2), X6.GND@4 (GND1)
unnamed: LED23.A, R36.2 (R2)
unnamed: JP8.3, X1.GND@1 (GND4), X1.GND@2 (GND3), X1.GND@3 (GND2), X1.GND@4 (GND1)
unnamed: JP10.3, X2.GND@1 (GND4), X2.GND@2 (GND3), X2.GND@3 (GND2), X2.GND@4 (GND1)
unnamed: JP8.2, X1.P (ANT)
unnamed: R3-1B1.2 (WIPER), R3-1B1.3 (CW), R3-2B1.1
unnamed: R3-2B1.2, R3-3B1.1
unnamed: R3-1A1.2 (WIPER), R3-1A1.3 (CW), R3-2A1.1
unnamed: R3-2A1.2, R3-3A1.1
unnamed: C1A1.+, R1A1.1, R4A1.1
unnamed: C1B1.+, R1B1.2, R4B1.1
unnamed: R2A1.2, R3-1A1.1 (CCW), U2.6 (-IN)
unnamed: R2B1.1, R3-1B1.1 (CCW), U2.2 (-IN)
unnamed: R4A1.2, U2.5 (+IN)
unnamed: R4B1.2, U2.3 (+IN)
unnamed: C1B2.+, R1B2.2, R4B2.1
unnamed: LED22.A, R35.2 (R2)
unnamed: LED24.A, R37.2 (R2)
unnamed: JP14.3, X7.GND@1 (GND4), X7.GND@2 (GND3), X7.GND@3 (GND2), X7.GND@4 (GND1)
unnamed: JP5.2, X20.2
unnamed: JP10.2, X2.P (ANT)
unnamed: JP5.3, X20.1
unnamed: JP2.3, X12.1
unnamed: JP2.2, X12.2
unnamed: JP12.2, X6.P (ANT)
unnamed: JP1.3, X11.1
unnamed: JP1.2, X11.2
unnamed: IC7.1 (VCC), JP16.1
unnamed: JP14.2, X7.P (ANT)
unnamed: D26.A, R39.5 (2)
unnamed: 12V.2 (R2), LED4.A
unnamed: LED7.A, R20.2 (R2)
unnamed: LED8.A, R21.2 (R2)
unnamed: LED9.A, R22.2 (R2)
unnamed: LED10.A, R23.2 (R2)
unnamed: LED11.A, R24.2 (R2)
unnamed: LED12.A, R25.2 (R2)
unnamed: LED13.A, R26.2 (R2)
unnamed: LED14.A, R27.2 (R2)
unnamed: LED15.A, R28.2 (R2)
unnamed: LED16.A, R29.2 (R2)
unnamed: LED17.A, R30.2 (R2)
unnamed: LED18.A, R31.2 (R2)
unnamed: LED19.A, R32.2 (R2)
unnamed: R3-1A2.2 (WIPER), R3-1A2.3 (CW), R3-2A2.1
unnamed: LED21.A, R34.2 (R2)
unnamed: LED25.A, R38.2 (R2)
unnamed: R3-2A2.2, R3-3A2.1
unnamed: LED27.A, R40.2 (R2)
unnamed: C1A2.+, R1A2.1, R4A2.1
unnamed: R2A2.2, R3-1A2.1 (CCW), U1.6 (-IN)
unnamed: R2B2.1, R3-1B2.1 (CCW), U1.2 (-IN)
unnamed: R4A2.2, U1.5 (+IN)
unnamed: R4B2.2, U1.3 (+IN)
unnamed: SJ3.2, U3.15 (A0)
unnamed: SJ2.2, U3.16 (A1)
unnamed: SJ1.2, U3.17 (A2)
OUT4: (0-10V)-2.2, R3-3B2.2, R37.1 (R1), U1.1 (OUT)
OUT-PUMP-1: D1.A, D5.C, IC1.2 (OUT1), PUMPBOX-1.1, R20.1 (R1)
OUT-PUMP-2: D2.A, D6.C, IC1.3 (OUT2), PUMPBOX-1.3, R21.1 (R1)
OUT-PUMP-3: D3.A, D7.C, IC1.13 (OUT3), PUMPBOX-1.5, R22.1 (R1)
OUT-PUMP-4: D4.A, D8.C, IC1.14 (OUT4), PUMPBOX-1.7, R23.1 (R1)
OUT-PUMP-5: D9.A, D13.C, IC2.2 (OUT1), PUMPBOX-2.1, R24.1 (R1)
OUT-PUMP-6: D10.A, D14.C, IC2.3 (OUT2), PUMPBOX-2.3, R25.1 (R1)
OUT-PUMP-7: D11.A, D15.C, IC2.13 (OUT3), PUMPBOX-2.5, R26.1 (R1)
OUT-PUMP-8: D12.A, D16.C, IC2.14 (OUT4), PUMPBOX-2.7, R27.1 (R1)
OUT-PUMP-9: D17.A, D21.C, IC3.2 (OUT1), PUMPBOX-3.1, R28.1 (R1)
OUT-PUMP-10: D18.A, D22.C, IC3.3 (OUT2), PUMPBOX-3.3, R29.1 (R1)
OUT-PUMP-11: D19.A, D23.C, IC3.13 (OUT3), PUMPBOX-3.5, R30.1 (R1)
OUT-PUMP-12: D20.A, D24.C, IC3.14 (OUT4), PUMPBOX-3.7, R31.1 (R1)
OUTA: R3-3A1.2, R32.1 (R1), U2.7 (OUT), X4.2
OUTA3: R3-3A2.2, R35.1 (R1), U1.7 (OUT), X3.2
OUTB: (0-10V)-1.2, R3-3B1.2, R34.1 (R1), U2.1 (OUT)
SCK: U3.12 (SCK)
SCL: IC7.6 (BUS1), J2.3, J3.3, J4.4, J5.4, J7.4, J8.4, J9.4, JP3.1, JP4.1, JP6.1, JP15.5, PUMPBOX-1.8, PUMPBOX-2.8, PUMPBOX-3.8, R7.3 (1), R9.3 (1), R11.3 (1), R13.3 (1), R39.2 (1), X13.3 (SCL1), X14.3 (SCL1), X16.3 (SCL1), X18.3 (SCL1), X21.1
SCL2: JP7.1, R10.3 (1), X13.6 (SCL2)
SCL3: JP9.1, R8.3 (1), X14.6 (SCL2)
SCL4: JP11.1, R12.3 (1), X16.6 (SCL2)
SCL5: JP13.1, R14.3 (1), X18.6 (SCL2)
SDA: IC7.4 (BUS2), J2.4, J3.4, J4.3, J5.3, J7.3, J8.3, J9.3, JP3.2, JP4.2, JP6.2, JP15.3, PUMPBOX-1.6, PUMPBOX-2.6, PUMPBOX-3.6, R7.2 (1), R9.2 (1), R11.2 (1), R13.2 (1), R39.1, U3.13 (SDA), X13.2 (SDA1), X14.2 (SDA1), X16.2 (SDA1), X18.2 (SDA1), X21.2
SDA2: JP7.2, R10.2 (1), X13.7 (SDA2)
SDA3: JP9.2, R8.2 (1), X14.7 (SDA2)
SDA4: JP11.2, R12.2 (1), X16.7 (SDA2)
SDA5: JP13.2, R14.2 (1), X18.7 (SDA2)

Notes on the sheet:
Power Isolation
Pump Control
PWM to Analog
EZO connectors non-isolated
Sensor and Screen Connector
Power and Data
3.3V Voltage Regulator
C3 helps in ripple rejection upto 15dB
D1 protect the device against input short circuit
D2 protect against output short circuit for capacitance discharging
C2 of 1 µF tantalum capacitor on the output helps to improve transient response
Useful Notes
3V to 40V DC
Vref = 1.25V
3.3V, 500mA
5V Voltage Regulator
5V, 500mA
Activity LED's
I2C Pullups & Shift
ON LED
Power supply

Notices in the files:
parts and their libraries:
microbuilder: This work is placed in the public domain, and may be freely used for commercial and non-commercial work with the following conditions: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
SparkFun-Connectors: Licensing: Creative Commons ShareAlike 4.0 International - https://creativecommons.org/licenses/by-sa/4.0
